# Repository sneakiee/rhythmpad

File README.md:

# rhythmpad

This was a YSWS project for Hack Club's hackpad for hack club's highway! I got the idea of creating a hackpad for rhythm games, but I also wanted to generalize it more for music, so I decided to make it into a drum-pad by creating square keycaps! The switches are mapped to the numpad from 1-9 and the extra button on the right being 0. This was my first actual hardware project and I hope to build more because it was a frustrating fun (I need to feel more of that.

# Schematic and PCB

# CAD

# Components
- 10x cherry mx switches
- 10x through-hole 1N4148 diodes
- 6x SK6812 MINI-E LEDs (unfortunately doesn't work with original files, but if SK6812MINI footprint in KiCad is changed, will work!)
- 1x seeeed XIAO RP2040
- 10x custom 3D printed keycaps
- custom 3D printed top case
- custom 3D printed middle case
- custom 3D printed bottom case
- 4x M3x16 Bolt
- 4x M3 Heatset

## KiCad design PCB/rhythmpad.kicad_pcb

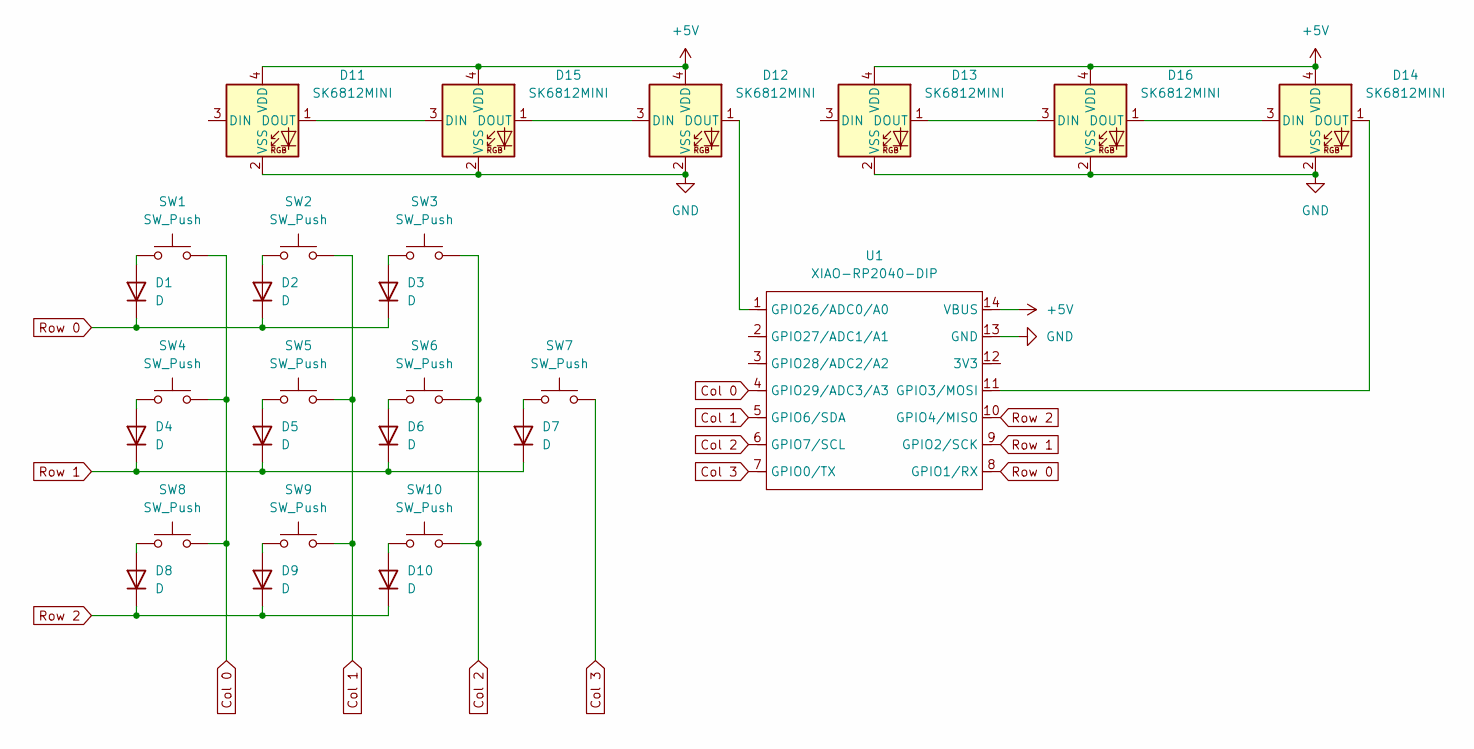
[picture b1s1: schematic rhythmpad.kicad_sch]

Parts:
D1, D2, D3, D4, D5, D6, D7, D8, D9, D10: D; D_DO-35_SOD27_P7.62mm_Horizontal
D11, D12, D13, D14, D15, D16: SK6812MINI; LED_SK6812MINI_PLCC4_3.5x3.5mm_P1.75mm
SW1, SW2, SW3, SW4, SW5, SW6, SW7, SW8, SW9, SW10: SW_Push; SW_Cherry_MX_1.00u_PCB
U1: XIAO-RP2040-DIP

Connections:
+5V: D11.4 (VDD), D12.4 (VDD), D13.4 (VDD), D14.4 (VDD), D15.4 (VDD), D16.4 (VDD), U1.14 (VBUS)
Col 0: SW1.2, SW4.2, SW8.2, U1.4 (GPIO29/ADC3/A3)
Col 1: SW2.2, SW5.2, SW9.2, U1.5 (GPIO6/SDA)
Col 2: SW3.2, SW6.2, SW10.2, U1.6 (GPIO7/SCL)
Col 3: SW7.2, U1.7 (GPIO0/TX)
GND: D11.2 (VSS), D12.2 (VSS), D13.2 (VSS), D14.2 (VSS), D15.2 (VSS), D16.2 (VSS), U1.13 (GND)
unnamed: D1.2 (A), SW1.1
unnamed: D2.2 (A), SW2.1
unnamed: D3.2 (A), SW3.1
unnamed: D4.2 (A), SW4.1
unnamed: D5.2 (A), SW5.1
unnamed: D6.2 (A), SW6.1
unnamed: D7.2 (A), SW7.1
unnamed: D8.2 (A), SW8.1
unnamed: D9.2 (A), SW9.1
unnamed: D10.2 (A), SW10.1
unnamed: D11.1 (DOUT), D15.3 (DIN)
unnamed: D12.3 (DIN), D15.1 (DOUT)
unnamed: D12.1 (DOUT), U1.1 (GPIO26/ADC0/A0)
unnamed: D13.1 (DOUT), D16.3 (DIN)
unnamed: D14.3 (DIN), D16.1 (DOUT)
unnamed: D14.1 (DOUT), U1.11 (GPIO3/MOSI)
Row 0: D1.1 (K), D2.1 (K), D3.1 (K), U1.8 (GPIO1/RX)
Row 1: D4.1 (K), D5.1 (K), D6.1 (K), D7.1 (K), U1.9 (GPIO2/SCK)
Row 2: D8.1 (K), D9.1 (K), D10.1 (K), U1.10 (GPIO4/MISO)

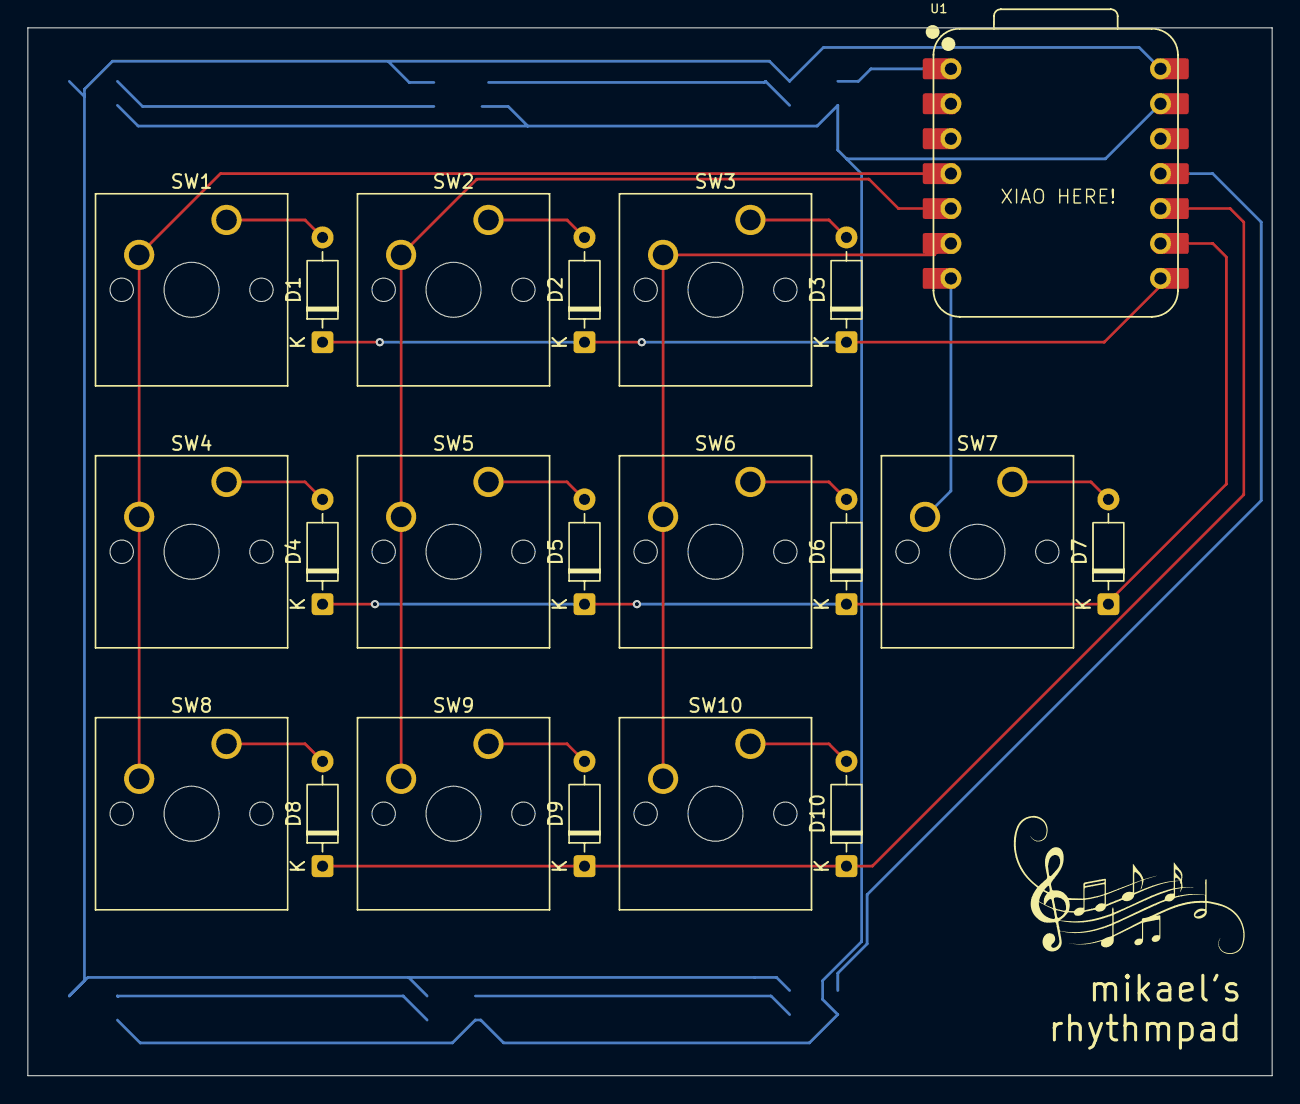
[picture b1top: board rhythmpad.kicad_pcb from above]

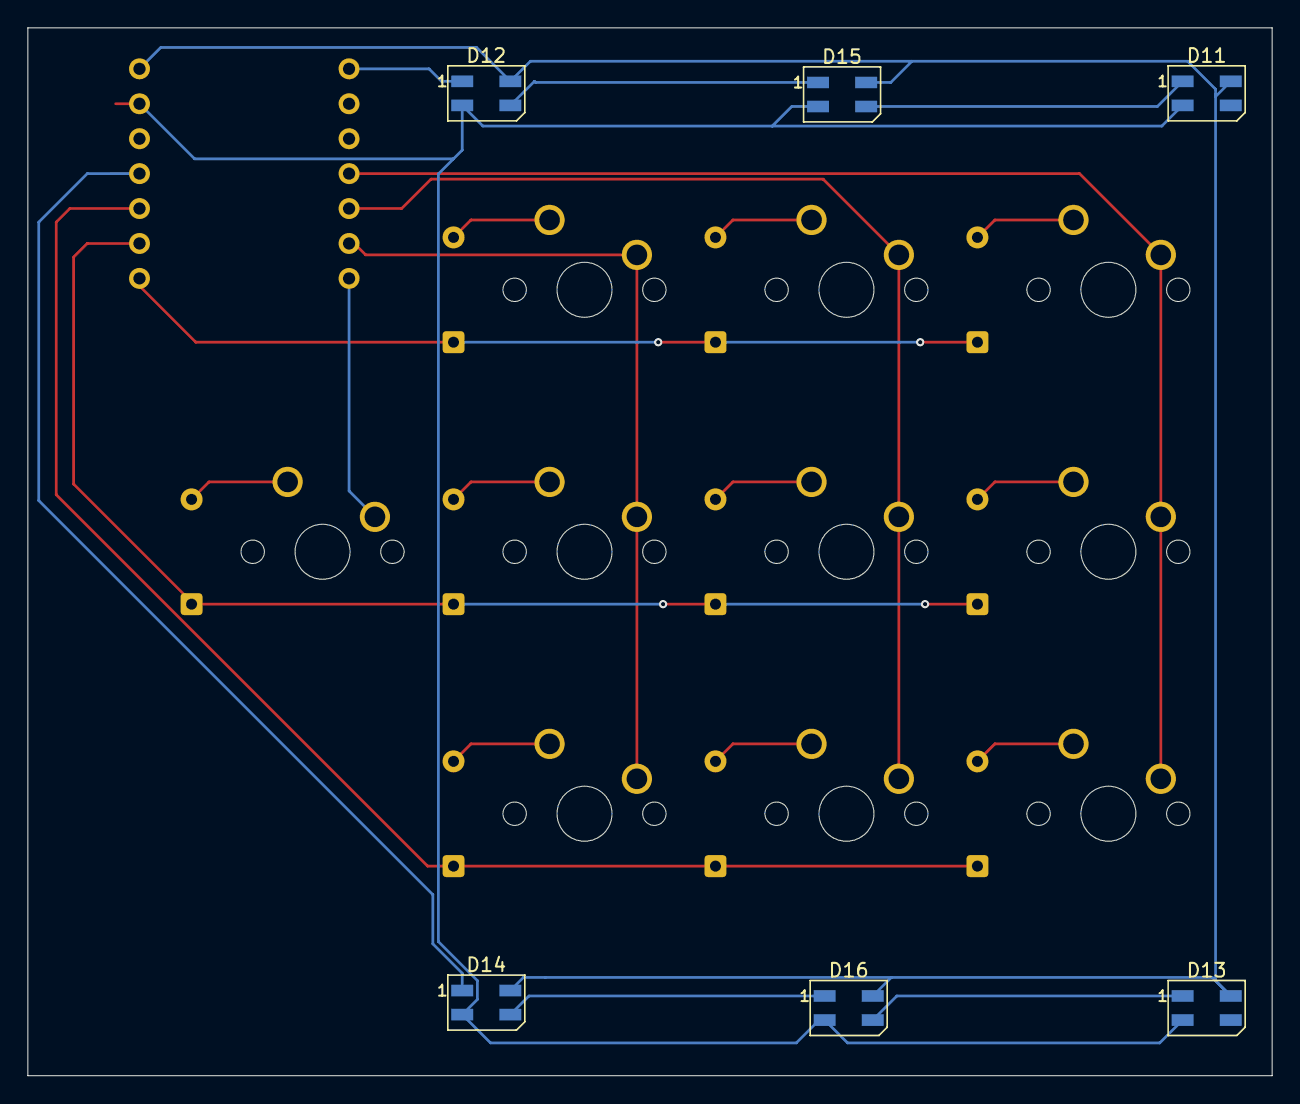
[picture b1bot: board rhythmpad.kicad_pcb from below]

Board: 2 copper layers, 90.5 x 76.2 mm, 27 parts (6 on the bottom side), 25 nets.

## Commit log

2025-06-12 upload kicad files
2025-06-12 add journal
2025-06-26 commit pcb/schematic changes
2025-06-26 update journal
2025-06-26 add library/finish pcb
2025-06-29 remove library
2025-06-29 remove journal images
2025-06-29 remove rhythmpad
2025-06-29 commit PCB/CAD/firmware/production
2025-06-29 upload firmware to production
2025-08-09 update firmware
2025-08-09 add led firmware
    if it did work you would use this firmware
